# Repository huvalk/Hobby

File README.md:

## Это репзиторий с разнообразными проектами по электронике и микропроцессорам

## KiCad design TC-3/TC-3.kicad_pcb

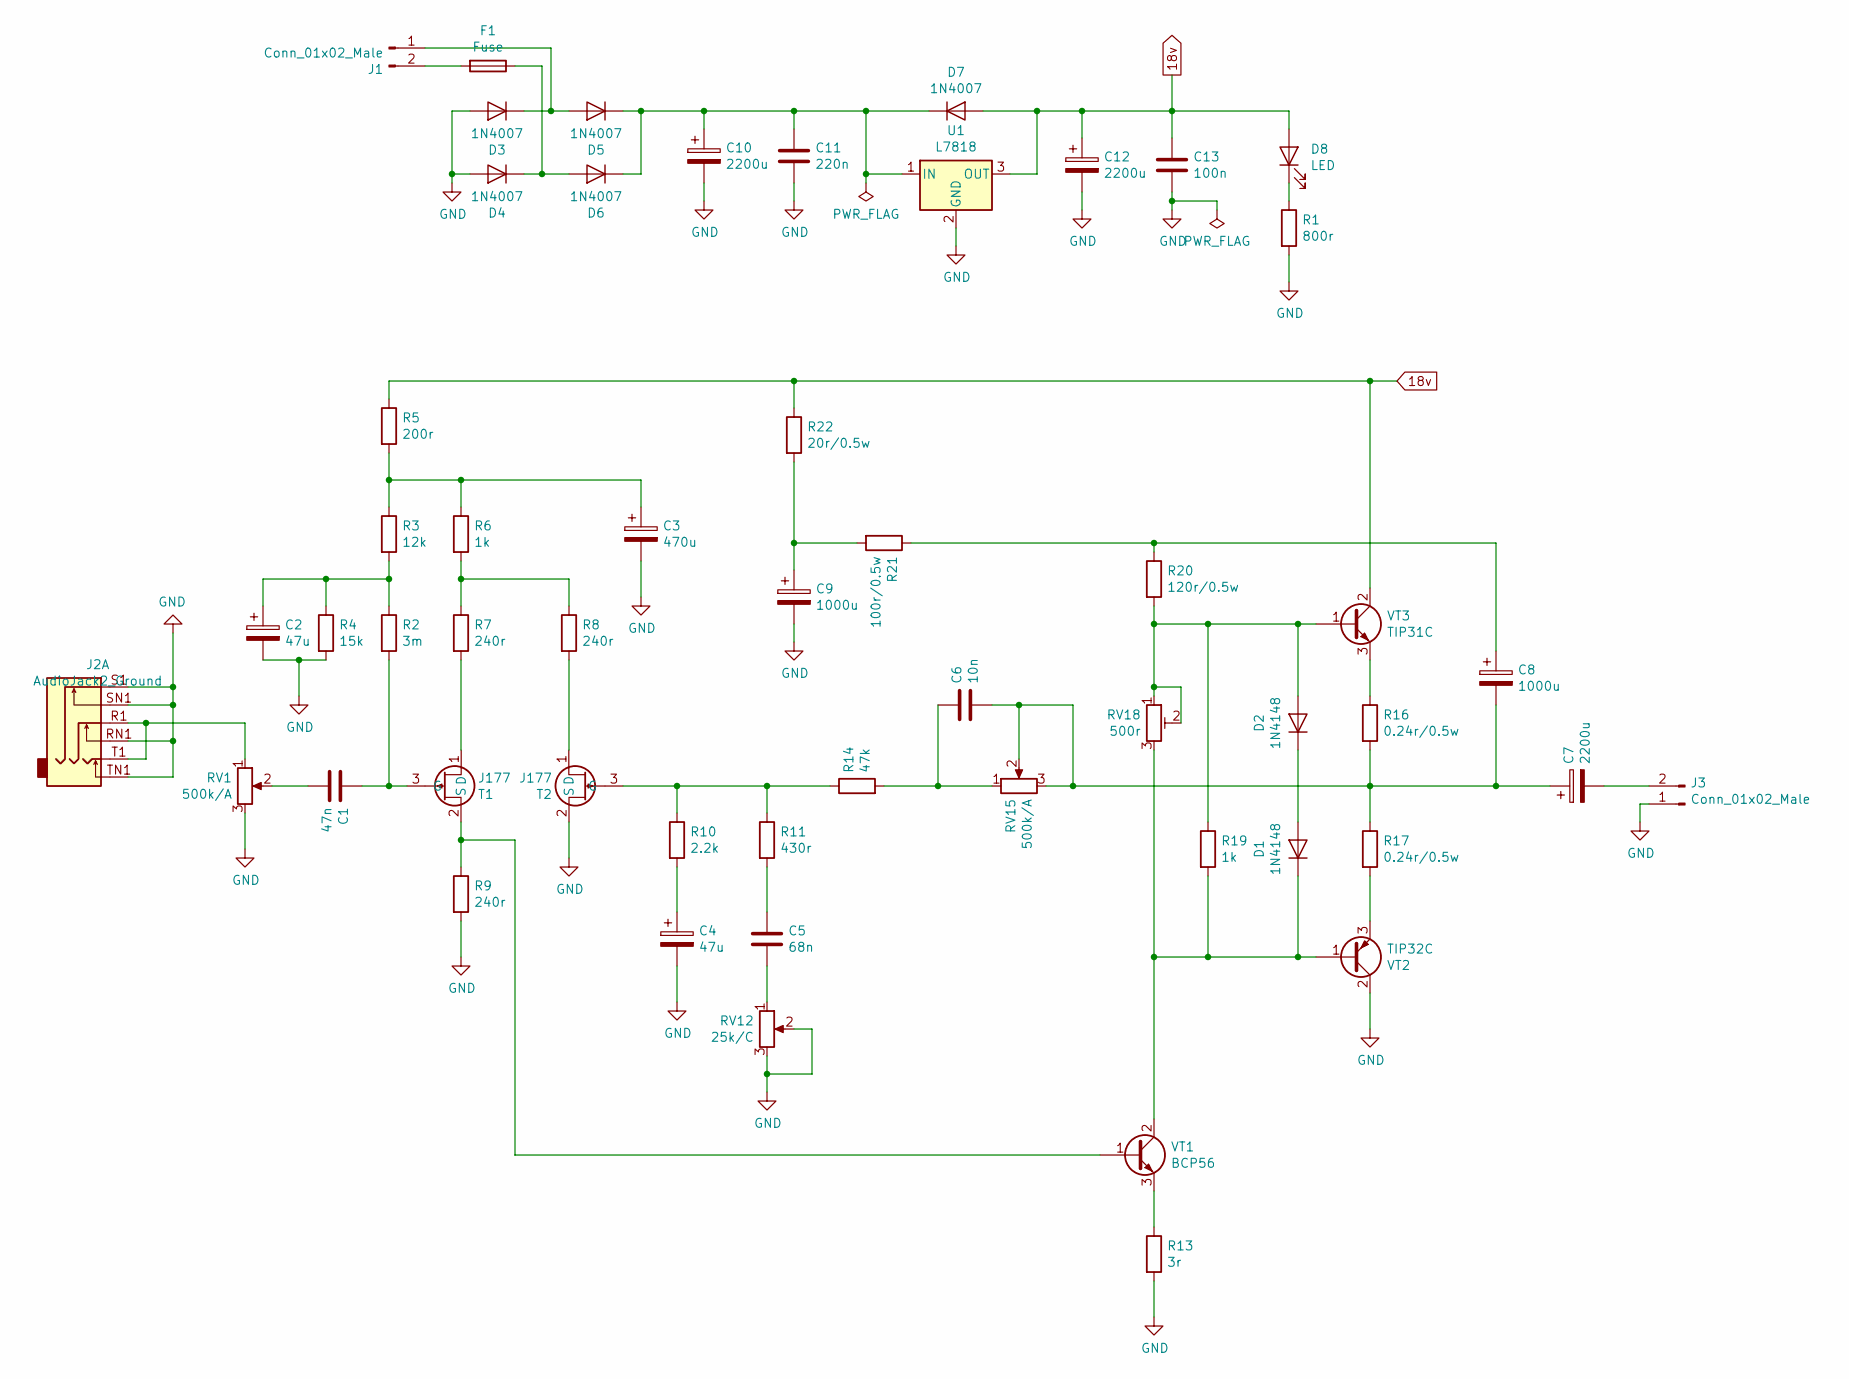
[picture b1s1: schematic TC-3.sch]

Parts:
C1: 47n; C_Rect_L7.0mm_W3.5mm_P5.00mm
C2, C4: 47u; CP_Radial_D8.0mm_P3.50mm
C3: 470u; CP_Radial_D10.0mm_P5.00mm
C5: 68n; C_Rect_L7.0mm_W3.5mm_P5.00mm
C6: 10n; C_Rect_L7.0mm_W3.5mm_P5.00mm
C7, C10, C12: 2200u; CP_Radial_D17.0mm_P7.50mm
C8, C9: 1000u; CP_Radial_D12.5mm_P5.00mm
C11: 220n; C_Rect_L7.0mm_W3.5mm_P5.00mm
C13: 100n; C_Rect_L7.0mm_W3.5mm_P5.00mm
D1, D2: 1N4148; D_DO-35_SOD27_P7.62mm_Horizontal
D3, D4, D5, D6, D7: 1N4007; D_DO-41_SOD81_P10.16mm_Horizontal
D8: LED; LED_D1.8mm_W1.8mm_H2.4mm_Horizontal_O3.81mm_Z1.6mm
F1: Fuse; Fuseholder_Blade_Mini_Keystone_3568
J1, J3: Conn_01x02_Male; JWT_A3963_1x02_P3.96mm_Vertical
J2: AudioJack2_Ground; Jack_3.5mm_Neutrik_NMJ6HCD2_Horizontal
R1: 800r; R_Axial_DIN0207_L6.3mm_D2.5mm_P7.62mm_Horizontal
R2: 3m; R_Axial_DIN0207_L6.3mm_D2.5mm_P7.62mm_Horizontal
R3: 12k; R_Axial_DIN0207_L6.3mm_D2.5mm_P7.62mm_Horizontal
R4: 15k; R_Axial_DIN0207_L6.3mm_D2.5mm_P7.62mm_Horizontal
R5: 200r; R_Axial_DIN0207_L6.3mm_D2.5mm_P7.62mm_Horizontal
R6, R19: 1k; R_Axial_DIN0207_L6.3mm_D2.5mm_P7.62mm_Horizontal
R7, R8, R9: 240r; R_Axial_DIN0207_L6.3mm_D2.5mm_P7.62mm_Horizontal
R10: 2.2k; R_Axial_DIN0207_L6.3mm_D2.5mm_P7.62mm_Horizontal
R11: 430r; R_Axial_DIN0207_L6.3mm_D2.5mm_P7.62mm_Horizontal
R13: 3r; R_Axial_DIN0207_L6.3mm_D2.5mm_P7.62mm_Horizontal
R14: 47k; R_Axial_DIN0207_L6.3mm_D2.5mm_P7.62mm_Horizontal
R16, R17: 0.24r/0.5w; R_Axial_DIN0309_L9.0mm_D3.2mm_P12.70mm_Horizontal
R20: 120r/0.5w; R_Axial_DIN0309_L9.0mm_D3.2mm_P12.70mm_Horizontal
R21: 100r/0.5w; R_Axial_DIN0309_L9.0mm_D3.2mm_P12.70mm_Horizontal
R22: 20r/0.5w; R_Axial_DIN0309_L9.0mm_D3.2mm_P12.70mm_Horizontal
RV1, RV15: 500k/A; Potentiometer_Piher_T-16H_Single_Horizontal
RV12: 25k/C; Potentiometer_Piher_T-16H_Single_Horizontal
RV18: 500r; Potentiometer_ACP_CA9-V10_Vertical
T1, T2: J177; SOT-23
U1: L7818; TO-220-3_Vertical
VT1: BCP56; SOT-223
VT2: TIP32C; TO-220-3_Vertical
VT3: TIP31C; TO-220-3_Vertical

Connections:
18v: C12.1, C13.1, D7.2 (A), D8.2 (A), R5.1, R22.1, U1.3 (OUT), VT3.2 (C)
GND: C2.2, C3.2, C4.2, C9.2, C10.2, C11.2, C12.2, C13.2, D3.2 (A), D4.2 (A), J2.RN1, J2.S1, J2.SN1, J2.TN1, J3.1, R1.2, R4.2, R9.2, R13.2, RV1.3, RV12.2, RV12.3, T2.2 (S), U1.2 (GND), VT2.2 (C)
unnamed: C1.1, R2.2, T1.3 (G)
unnamed: C1.2, RV1.2
unnamed: C2.1, R2.1, R3.2, R4.1
unnamed: C3.1, R3.1, R5.2, R6.1
unnamed: C4.1, R10.2
unnamed: C5.1, R11.2
unnamed: C5.2, RV12.1
unnamed: C6.1, R14.2, RV15.1
unnamed: C6.2, C7.1, C8.2, R16.2, R17.1, RV15.2, RV15.3
unnamed: C7.2, J3.2
unnamed: C8.1, R20.1, R21.1
unnamed: C9.1, R21.2, R22.2
unnamed: C10.1, C11.1, D5.1 (K), D6.1 (K), D7.1 (K), U1.1 (IN)
unnamed: D1.1 (K), R19.2, RV18.3, VT1.2 (C), VT1.4 (C), VT2.1 (B)
unnamed: D1.2 (A), D2.1 (K)
unnamed: D2.2 (A), R19.1, R20.2, RV18.1, RV18.2, VT3.1 (B)
unnamed: D3.1 (K), D5.2 (A), J1.1
unnamed: D4.1 (K), D6.2 (A), F1.1
unnamed: D8.1 (K), R1.1
unnamed: F1.2, J1.2
unnamed: J2.R1, J2.T1, RV1.1
unnamed: R6.2, R7.1, R8.1
unnamed: R9.1, T1.2 (S), VT1.1 (B)
unnamed: R10.1, R11.1, R14.1, T2.3 (G)
unnamed: R13.1, VT1.3 (E)
unnamed: R16.1, VT3.3 (E)
unnamed: R17.2, VT2.3 (E)

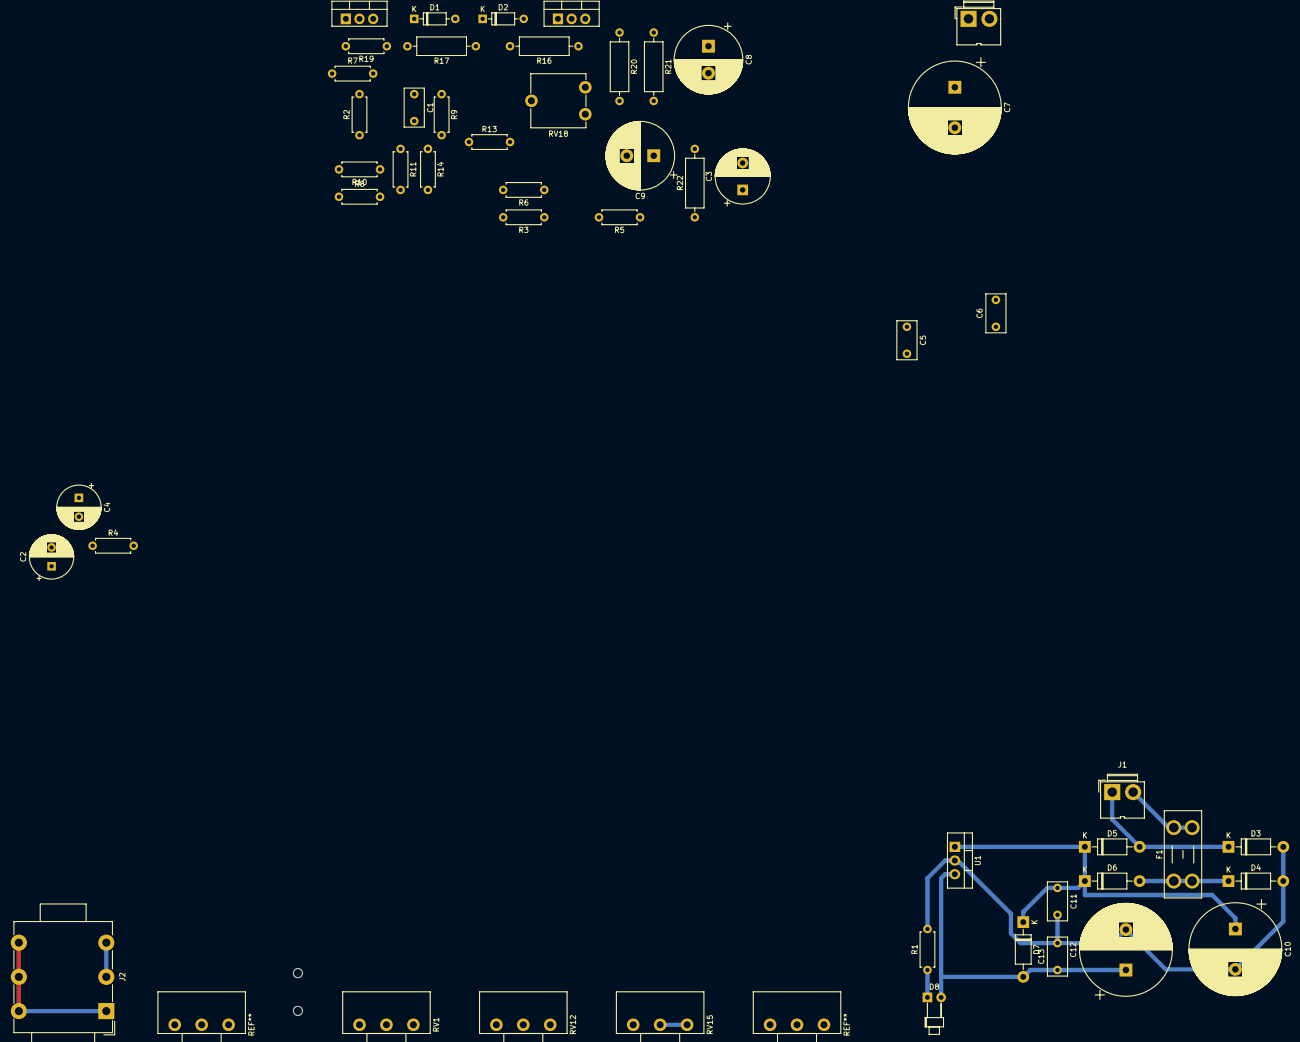
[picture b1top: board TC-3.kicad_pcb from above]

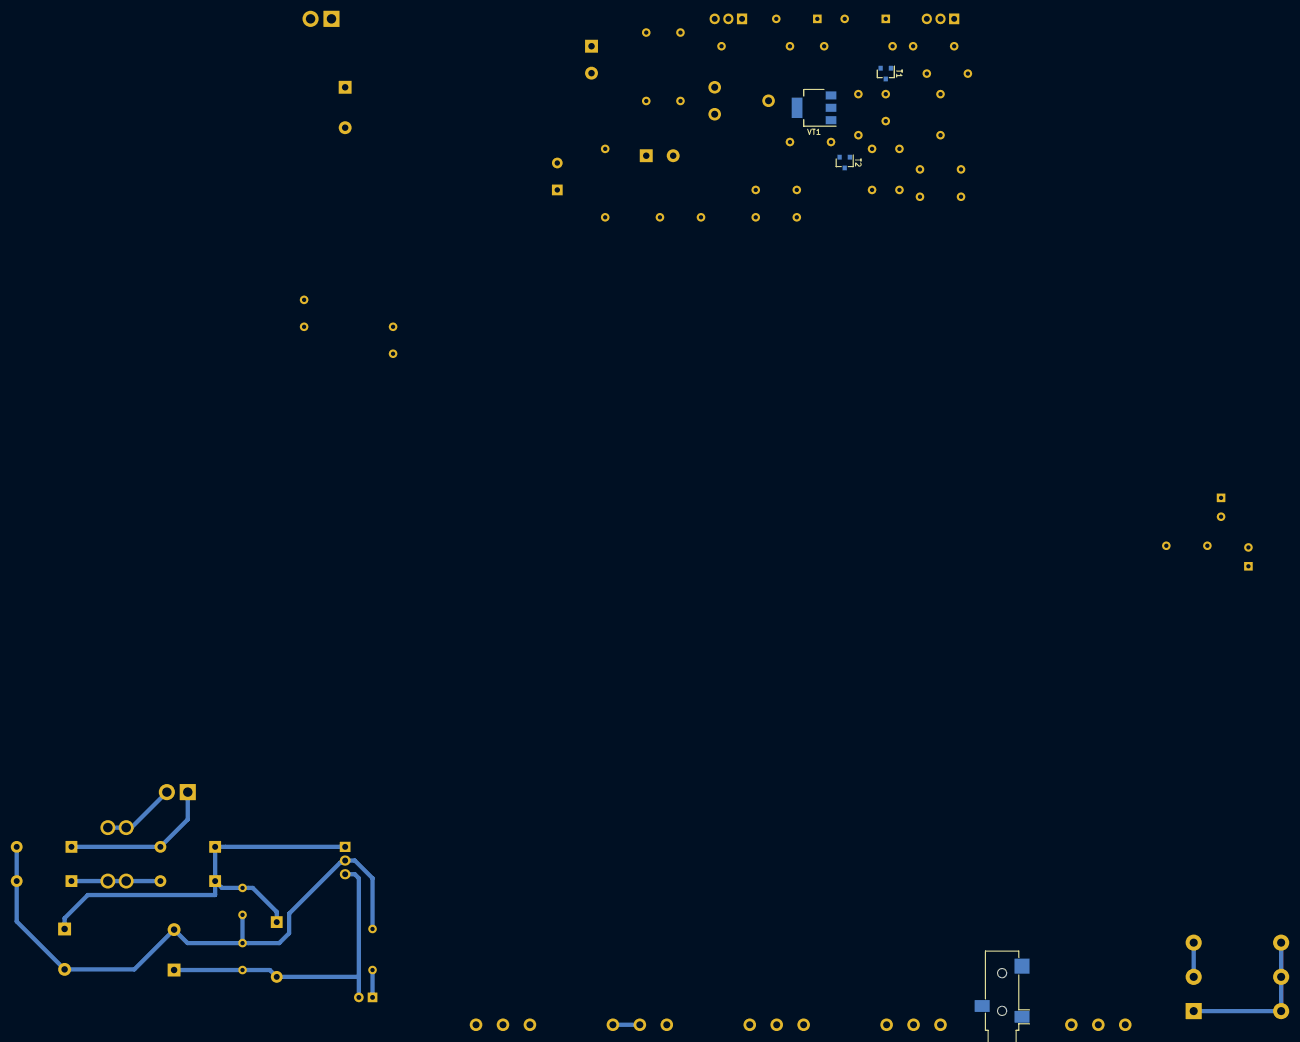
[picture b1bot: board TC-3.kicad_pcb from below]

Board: 2 copper layers, 54 parts (3 on the bottom side), 29 nets.

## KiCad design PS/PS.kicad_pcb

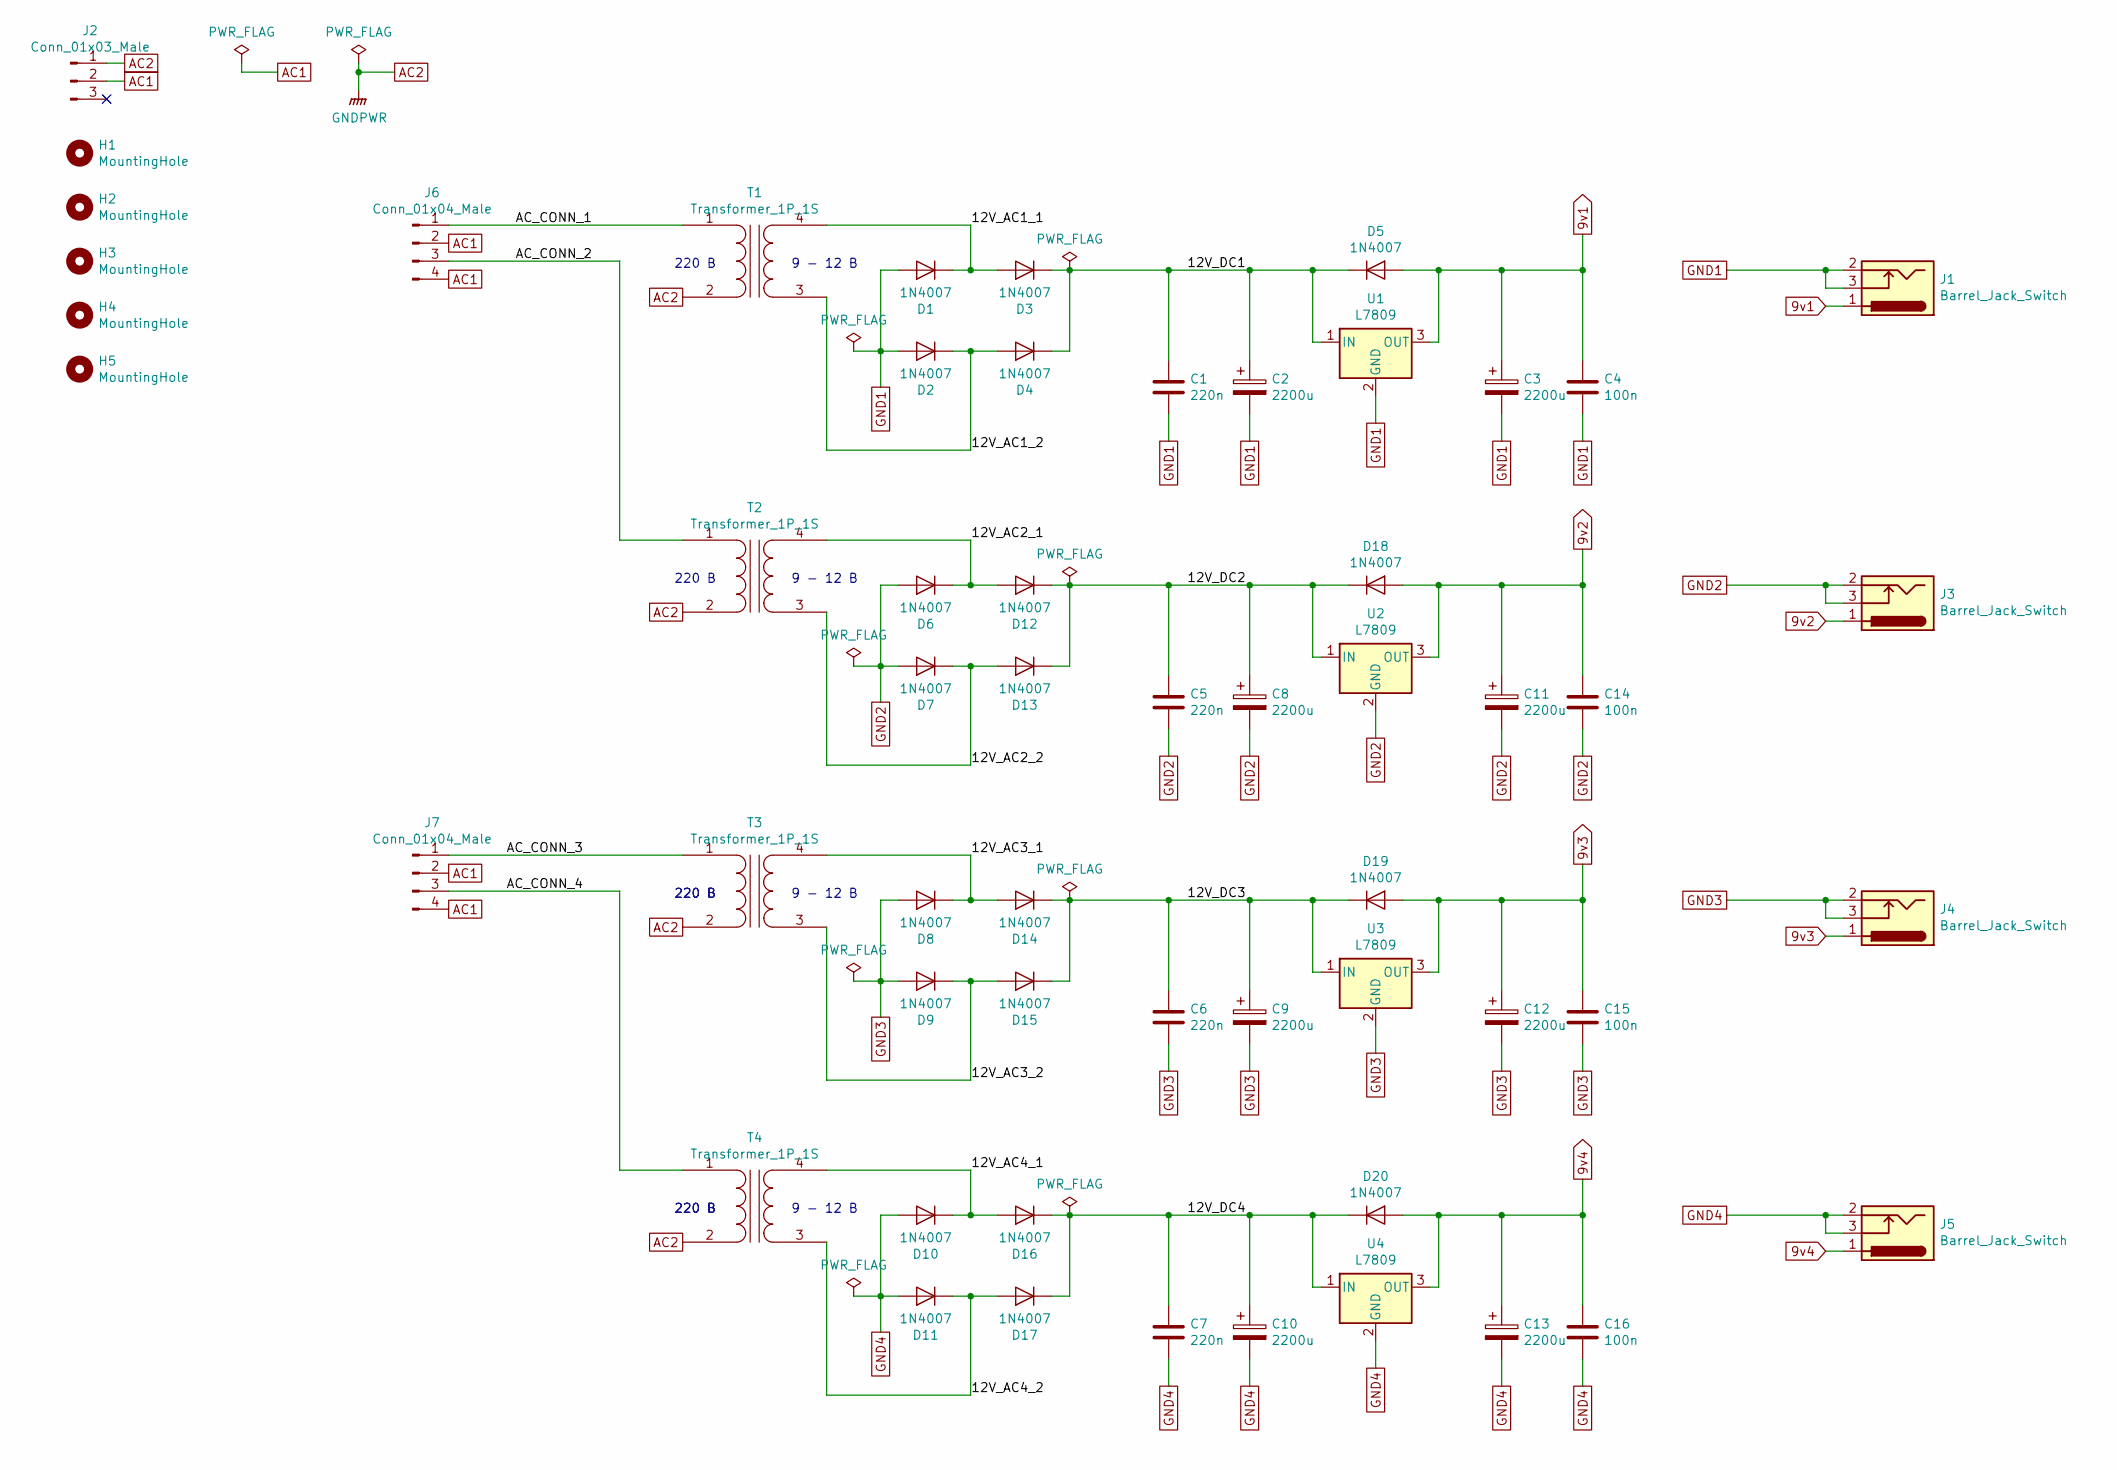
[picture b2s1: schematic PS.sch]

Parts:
C1, C5, C6, C7: 220n; C_Rect_L7.0mm_W3.5mm_P5.00mm
C2, C3, C8, C9, C10, C11, C12, C13: 2200u; CP_Radial_D17.0mm_P7.50mm
C4, C14, C15, C16: 100n; C_Rect_L7.0mm_W3.5mm_P5.00mm
D1, D2, D3, D4, D5, D6, D7, D8, D9, D10, D11, D12, D13, D14, D15, D16, D17, D18, D19, D20: 1N4007; D_DO-41_SOD81_P7.62mm_Horizontal
H1, H2, H3, H4, H5: MountingHole; MountingHole_3.2mm_M3_DIN965_Pad
J1, J3, J4, J5: Barrel_Jack_Switch; DC_BarrelJack
J2: Conn_01x03_Male; AS-205
J6, J7: Conn_01x04_Male; PinHeader_1x04_P2.54mm_Vertical
T1, T2, T3, T4: Transformer_1P_1S; Transformer_20x40
U1, U2, U3, U4: L7809; TO-220-3_Vertical

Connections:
9v1: C3.1, C4.1, D5.2 (A), J1.1, U1.3 (OUT)
9v2: C11.1, C14.1, D18.2 (A), J3.1, U2.3 (OUT)
9v3: C12.1, C15.1, D19.2 (A), J4.1, U3.3 (OUT)
9v4: C13.1, C16.1, D20.2 (A), J5.1, U4.3 (OUT)
/12V_AC1_1: D1.1 (K), D3.2 (A), T1.4 (SB)
/12V_AC1_2: D2.1 (K), D4.2 (A), T1.3 (SA)
/12V_AC2_1: D6.1 (K), D12.2 (A), T2.4 (SB)
/12V_AC2_2: D7.1 (K), D13.2 (A), T2.3 (SA)
/12V_AC3_1: D8.1 (K), D14.2 (A), T3.4 (SB)
/12V_AC3_2: D9.1 (K), D15.2 (A), T3.3 (SA)
/12V_AC4_1: D10.1 (K), D16.2 (A), T4.4 (SB)
/12V_AC4_2: D11.1 (K), D17.2 (A), T4.3 (SA)
/12V_DC1: C1.1, C2.1, D3.1 (K), D4.1 (K), D5.1 (K), U1.1 (IN)
/12V_DC2: C5.1, C8.1, D12.1 (K), D13.1 (K), D18.1 (K), U2.1 (IN)
/12V_DC3: C6.1, C9.1, D14.1 (K), D15.1 (K), D19.1 (K), U3.1 (IN)
/12V_DC4: C7.1, C10.1, D16.1 (K), D17.1 (K), D20.1 (K), U4.1 (IN)
/AC_CONN_1: J6.1, T1.1 (AA)
/AC_CONN_2: J6.3, T2.1 (AA)
/AC_CONN_3: J7.1, T3.1 (AA)
/AC_CONN_4: J7.3, T4.1 (AA)
AC1: J2.2, J6.2, J6.4, J7.2, J7.4
AC2: J2.1, T1.2 (AB), T2.2 (AB), T3.2 (AB), T4.2 (AB)
GND1: C1.2, C2.2, C3.2, C4.2, D1.2 (A), D2.2 (A), J1.2, J1.3, U1.2 (GND)
GND2: C5.2, C8.2, C11.2, C14.2, D6.2 (A), D7.2 (A), J3.2, J3.3, U2.2 (GND)
GND3: C6.2, C9.2, C12.2, C15.2, D8.2 (A), D9.2 (A), J4.2, J4.3, U3.2 (GND)
GND4: C7.2, C10.2, C13.2, C16.2, D10.2 (A), D11.2 (A), J5.2, J5.3, U4.2 (GND)

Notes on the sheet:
9 - 12 В
220 В

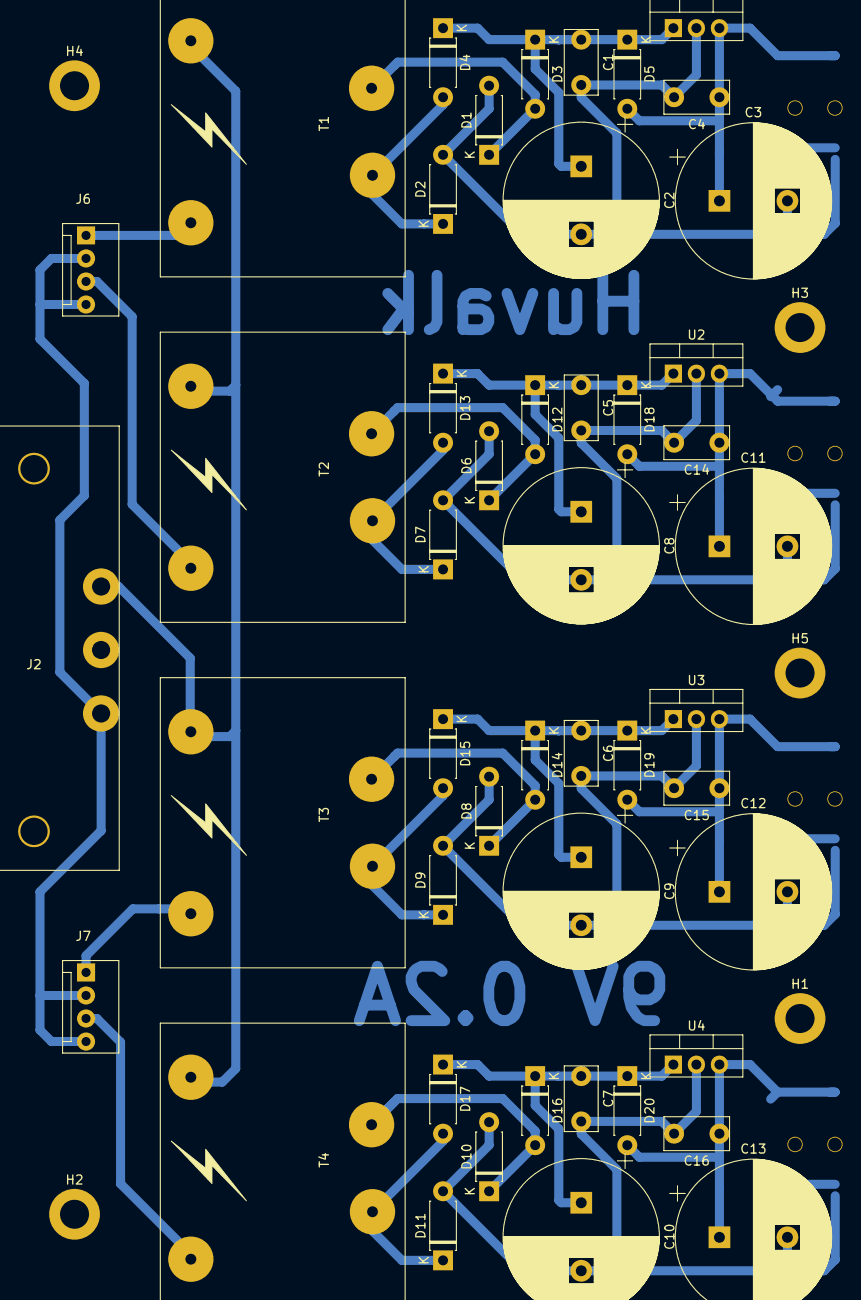
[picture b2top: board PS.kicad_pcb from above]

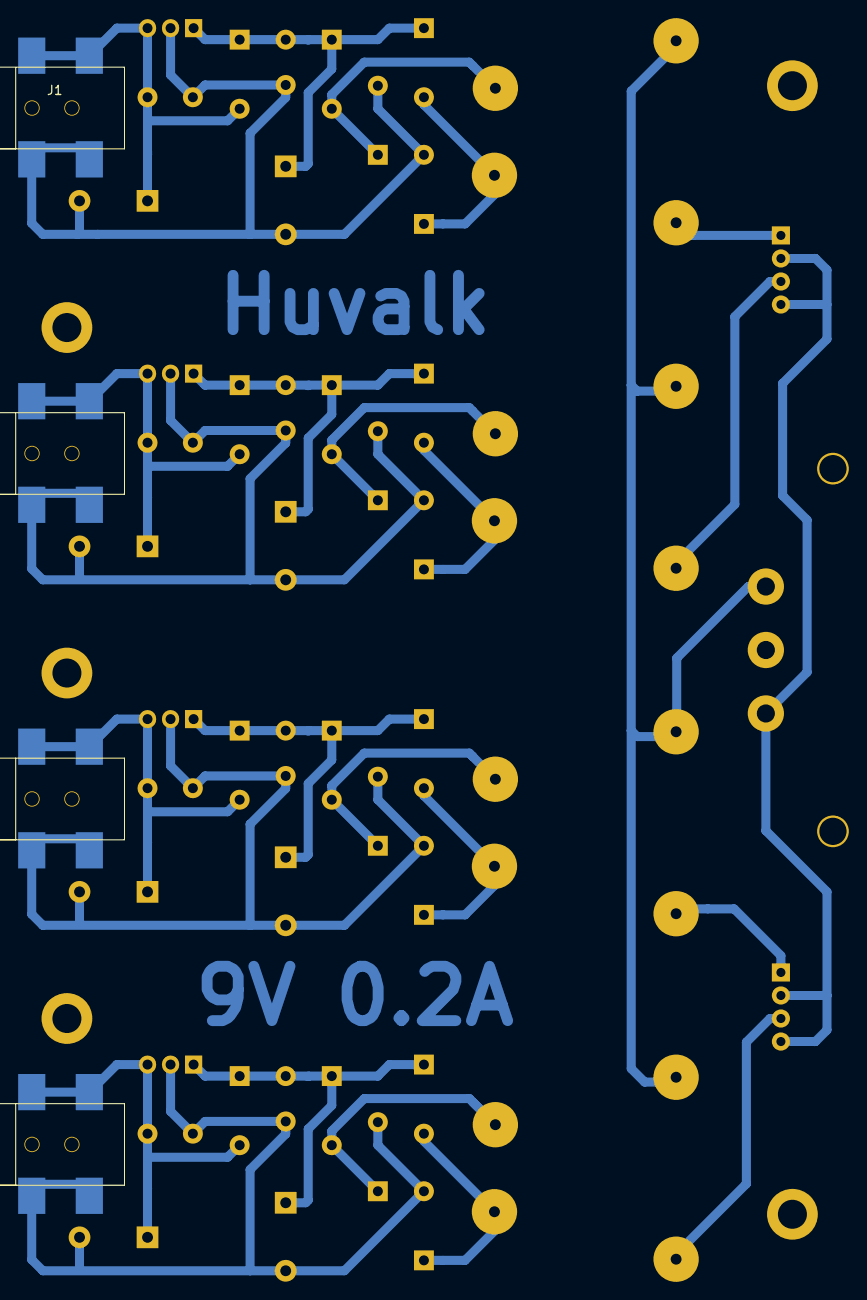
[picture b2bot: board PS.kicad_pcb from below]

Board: 2 copper layers, 56 parts (4 on the bottom side), 26 nets.

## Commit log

2022-09-29 init
